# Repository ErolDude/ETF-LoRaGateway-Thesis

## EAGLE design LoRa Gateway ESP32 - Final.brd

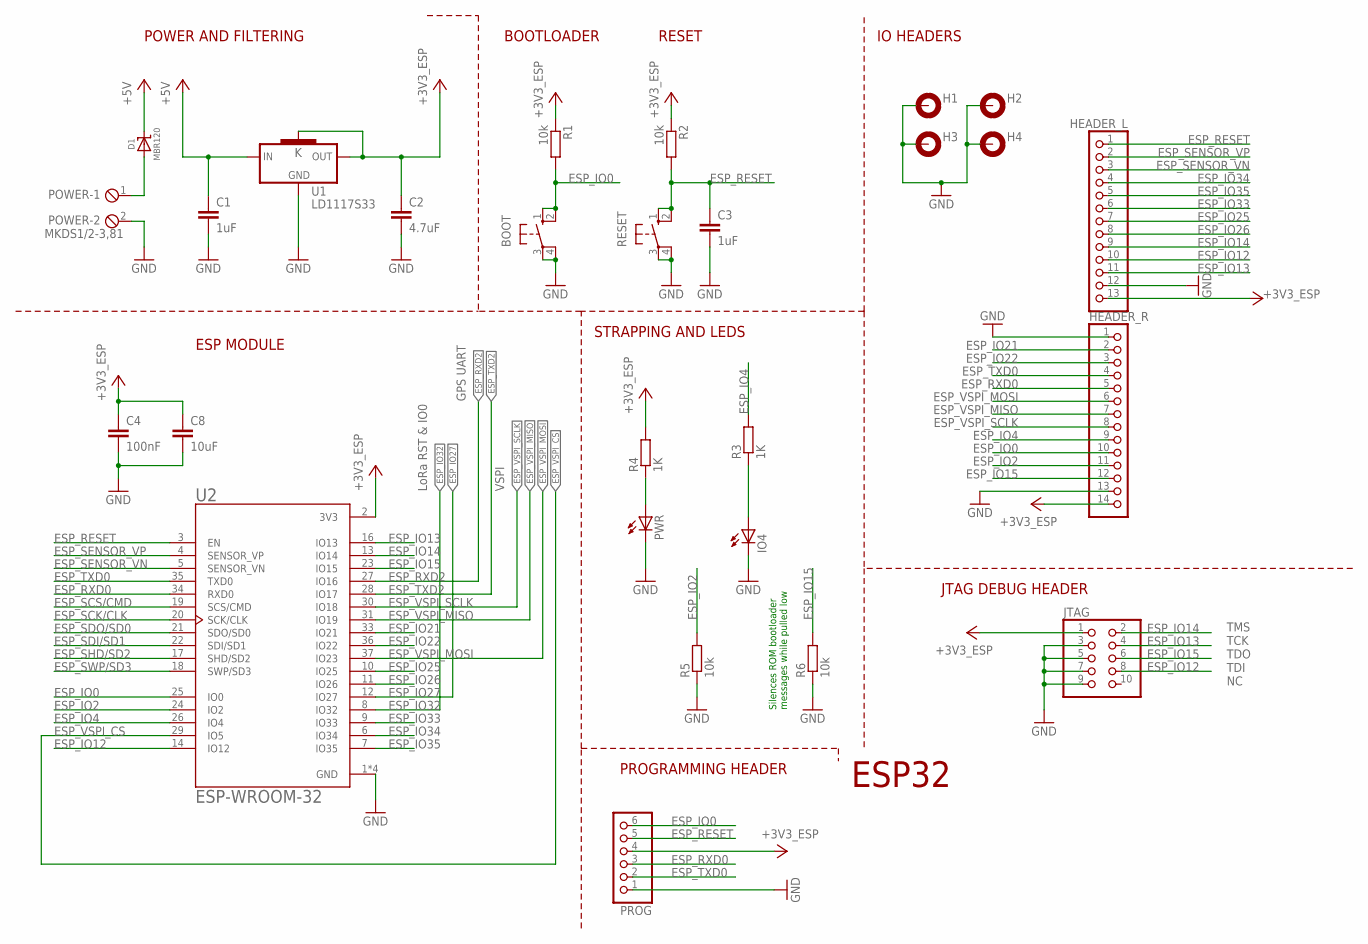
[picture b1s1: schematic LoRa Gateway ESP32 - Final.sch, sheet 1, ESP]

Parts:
BOOT: 10-XX; B3F-10XX
C1, C3: 1uF; C0805K
C2: 4.7uF; C0805K
C4: 100nF; C0805K
C8: 10uF; C0805K
D1: MBR120; SOD-123
H1, H2, H3, H4: MOUNT-PAD-ROUND3.2; 3,2-PAD
HEADER_L: PINHD-1X13; 1X13
HEADER_R: PINHD-1X14; 1X14
IO4: LEDCHIP-LED0805; CHIP-LED0805
JTAG: PINHD-2X5; 2X05
POWER: MKDS1/2-3,81; 2POL381
PROG: PINHD-1X6; 1X06
PWR: LEDCHIP-LED0805; CHIP-LED0805
R1, R2, R5, R6: 10k; R0805
R3, R4: 1K; R0805
RESET: 10-XX; B3F-10XX
U1: LD1117S33; SOT223
U2: ESP-WROOM-32; MODULE_ESP-WROOM-32

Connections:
+3V3_ESP: C2.1, C4.1, C8.1, HEADER_L.13, HEADER_R.14, JTAG.1, PROG.4, R1.1, R2.1, R4.2, U1.2 (OUT), U1.4 (K), U2.2 (3V3); also elsewhere on the board
+5V: C1.1, D1.C, U1.3 (IN)
ESP_IO0: BOOT.1 (S), BOOT.2 (S1), HEADER_R.10, PROG.6, R1.2, U2.25 (IO0)
ESP_IO2: HEADER_R.11, R5.2, U2.24 (IO2)
ESP_IO4: HEADER_R.9, R3.2, U2.26 (IO4)
ESP_IO12: HEADER_L.10, JTAG.8, U2.14 (IO12)
ESP_IO13: HEADER_L.11, JTAG.4, U2.16 (IO13)
ESP_IO14: HEADER_L.9, JTAG.2, U2.13 (IO14)
ESP_IO15: HEADER_R.12, JTAG.6, R6.2, U2.23 (IO15)
ESP_IO21: HEADER_R.2, U2.33 (IO21)
ESP_IO22: HEADER_R.3, U2.36 (IO22)
ESP_IO25: HEADER_L.7, U2.10 (IO25)
ESP_IO26: HEADER_L.8, U2.11 (IO26)
ESP_IO27: U2.12 (IO27); also elsewhere on the board
ESP_IO32: U2.8 (IO32); also elsewhere on the board
ESP_IO33: HEADER_L.6, U2.9 (IO33)
ESP_IO34: HEADER_L.4, U2.6 (IO34)
ESP_IO35: HEADER_L.5, U2.7 (IO35)
ESP_RESET: C3.1, HEADER_L.1, PROG.5, R2.2, RESET.1 (S), RESET.2 (S1), U2.3 (EN)
ESP_RXD0: HEADER_R.5, PROG.3, U2.34 (RXD0)
ESP_RXD2: U2.27 (IO16); also elsewhere on the board
ESP_SCK/CLK: U2.20 (SCK/CLK)
ESP_SCS/CMD: U2.19 (SCS/CMD)
ESP_SDI/SD1: U2.22 (SDI/SD1)
ESP_SDO/SD0: U2.21 (SDO/SD0)
ESP_SENSOR_VN: HEADER_L.3, U2.5 (SENSOR_VN)
ESP_SENSOR_VP: HEADER_L.2, U2.4 (SENSOR_VP)
ESP_SHD/SD2: U2.17 (SHD/SD2)
ESP_SWP/SD3: U2.18 (SWP/SD3)
ESP_TXD0: HEADER_R.4, PROG.2, U2.35 (TXD0)
ESP_TXD2: U2.28 (IO17); also elsewhere on the board
ESP_VSPI_CS: U2.29 (IO5); also elsewhere on the board
ESP_VSPI_MISO: HEADER_R.7, U2.31 (IO19); also elsewhere on the board
ESP_VSPI_MOSI: HEADER_R.6, U2.37 (IO23); also elsewhere on the board
ESP_VSPI_SCLK: HEADER_R.8, U2.30 (IO18); also elsewhere on the board
GND: BOOT.3, BOOT.4 (P1), C1.2, C2.2, C3.2, C4.2, C8.2, H1.B3,2, H2.B3,2, H3.B3,2, H4.B3,2, HEADER_L.12, HEADER_R.1, HEADER_R.13, IO4.C, JTAG.3, JTAG.5, JTAG.7, JTAG.9, POWER.2, PROG.1, PWR.C, R5.1, R6.1, RESET.3, RESET.4 (P1), U1.1 (GND), U2.1 (GND), U2.1.1 (GND), U2.15 (GND), U2.38 (GND); also elsewhere on the board
unnamed: D1.A, POWER.1
unnamed: IO4.A, R3.1
unnamed: PWR.A, R4.1

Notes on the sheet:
Silences ROM bootloader messages while pulled low
GPS UART
VSPI
LoRa RST & IO0
ESP32
JTAG DEBUG HEADER
IO HEADERS
STRAPPING AND LEDS
ESP MODULE
POWER AND FILTERING
BOOTLOADER
RESET
PROGRAMMING HEADER
TMS TCK TDO TDI NC

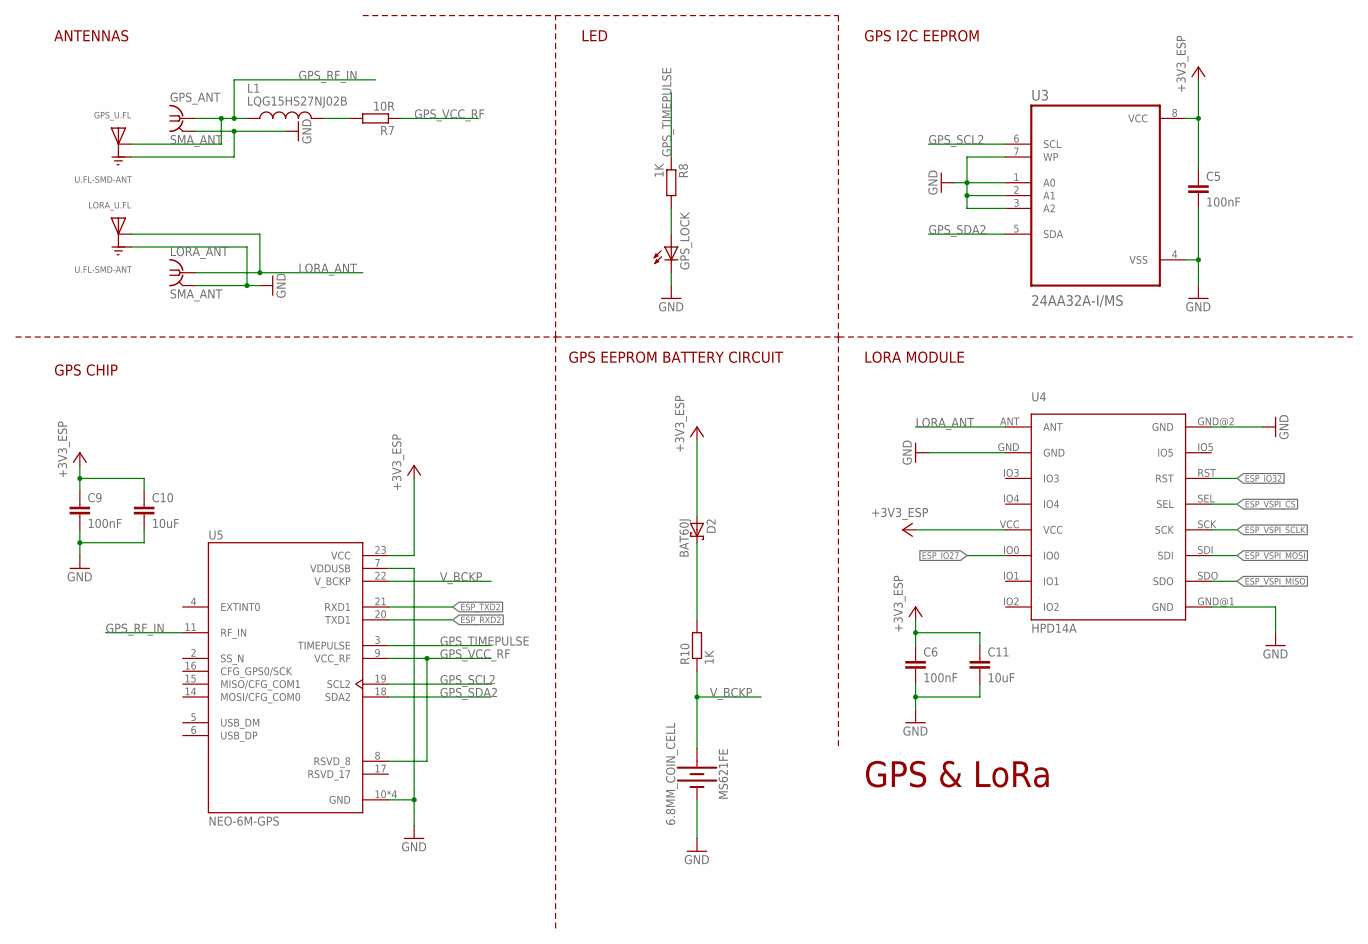
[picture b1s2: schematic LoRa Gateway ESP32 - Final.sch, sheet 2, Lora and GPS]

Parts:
C5, C6, C9: 100nF; C0805K
C10, C11: 10uF; C0805K
D2: BAT60J; SOD323_ST
GPS_ANT: SMA_ANT; BU-SMA-H
GPS_LOCK: LEDCHIP-LED0805; CHIP-LED0805
GPS_U.FL: U.FL-SMD-ANT; HRS_U.FL-R-SMT-1(10)
L1: LQG15HS27NJ02B; INDC1005X55N
LORA_ANT: SMA_ANT; BU-SMA-H
LORA_U.FL: U.FL-SMD-ANT; HRS_U.FL-R-SMT-1(10)
MS621FE: 6.8MM_COIN_CELL; BATTCON-6.8MM
R7: 10R; R0805
R8, R10: 1K; R0805
U3: 24AA32A-I/MS; SOP65P490X110-8N
U4: HPD14A
U5: NEO-6M-GPS; XCVR_NEO-6M-GPS

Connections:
+3V3_ESP: C5.1, C6.1, C9.1, C10.1, C11.1, D2.A, U3.8 (VCC), U4.VCC, U5.23 (VCC); also elsewhere on the board
ESP_IO27: U4.IO0; also elsewhere on the board
ESP_IO32: U4.RST; also elsewhere on the board
ESP_RXD2: U5.20 (TXD1); also elsewhere on the board
ESP_TXD2: U5.21 (RXD1); also elsewhere on the board
ESP_VSPI_CS: U4.SEL; also elsewhere on the board
ESP_VSPI_MISO: U4.SDO; also elsewhere on the board
ESP_VSPI_MOSI: U4.SDI; also elsewhere on the board
ESP_VSPI_SCLK: U4.SCK; also elsewhere on the board
GND: C5.2, C6.2, C9.2, C10.2, C11.2, GPS_ANT.2, GPS_ANT.3 (2), GPS_ANT.4 (2), GPS_ANT.5 (2), GPS_LOCK.C, GPS_U.FL.1 (GND), GPS_U.FL.3 (GND), LORA_ANT.2, LORA_ANT.3 (2), LORA_ANT.4 (2), LORA_ANT.5 (2), LORA_U.FL.1 (GND), LORA_U.FL.3 (GND), MS621FE.-, U3.1 (A0), U3.2 (A1), U3.3 (A2), U3.4 (VSS), U3.7 (WP), U4.GND, U4.GND@1 (GND), U4.GND@2 (GND), U5.7 (VDDUSB), U5.10 (GND), U5.12 (GND), U5.13 (GND), U5.24 (GND); also elsewhere on the board
GPS_RF_IN: GPS_ANT.1, GPS_U.FL.2 (SIG), L1.1, U5.11 (RF_IN)
GPS_SCL2: U3.6 (SCL), U5.19 (SCL2)
GPS_SDA2: U3.5 (SDA), U5.18 (SDA2)
GPS_TIMEPULSE: R8.1, U5.3 (TIMEPULSE)
GPS_VCC_RF: R7.1, U5.8 (RSVD_8), U5.9 (VCC_RF)
LORA_ANT: LORA_ANT.1, LORA_U.FL.2 (SIG), U4.ANT
unnamed: GPS_LOCK.A, R8.2
unnamed: L1.2, R7.2
unnamed: D2.C, R10.2
V_BCKP: MS621FE.+, R10.1, U5.22 (V_BCKP)

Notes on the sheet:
GPS & LoRa
GPS CHIP
LORA MODULE
GPS EEPROM BATTERY CIRCUIT
ANTENNAS
LED
GPS I2C EEPROM

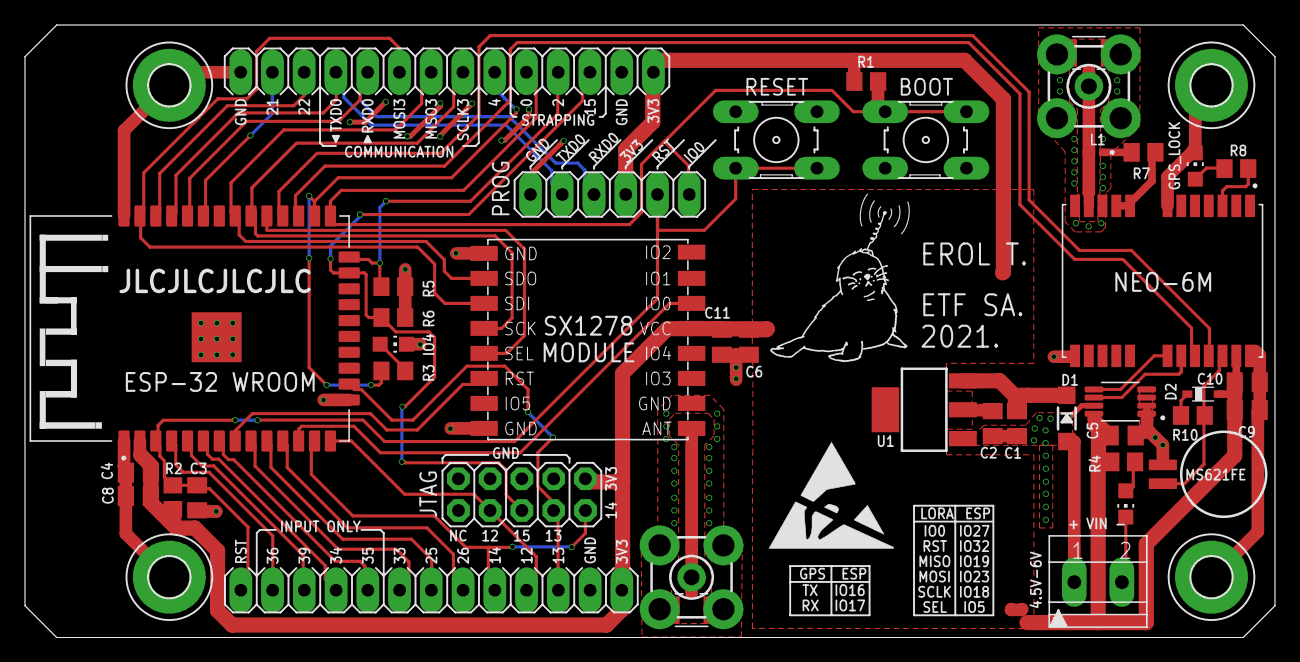
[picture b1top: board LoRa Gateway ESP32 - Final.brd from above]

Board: 2 copper layers, 100.0 x 49.0 mm, 47 parts (0 on the bottom side), 43 nets.

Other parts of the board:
U$1: ESD_10.00

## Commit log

2021-06-04 Production update
    Added production variant of board and schematic. Also added gerber files used to order board
2021-06-24 Added thesis draft
    Work in progress
2021-06-24 Added "written documents" folder
2021-07-16 Final version update for written material
